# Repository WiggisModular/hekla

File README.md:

# hekla

FeatherWing Eurorack module, optimised for the Feather M4 express. I designed it to act as a slow LFO using DAC0 and DAC1 for two channels. 

## Resources (AKA giants on which shoulder I built)

### Featherwing

https://forum.kicad.info/t/designing-featherwings-in-kicad/6115/2

### Outputs and stuff: 

https://blog.thea.codes/designing-big-honking-button/

BTW: Follow her on twitter, read her blog, buy her modules. Wholesome content from a kickass person.

### Frontpanel copper layer 

Original data https://commons.wikimedia.org/wiki/File:Hekla1980.jpg#/media/File:Hekla1980.jpg

## Production files

Gerber, a schematic and a placement drawing, as well as a BOM and a pick and place file to get the SMD parts assembled over at JLCPCB will be available as releases as soon as I tested the first batch.

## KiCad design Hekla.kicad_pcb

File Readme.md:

# Parsel 

FeatherWing Eurorack module, optimised for the Feather M4 express. I designed it to act as a slow LFO using DAC0 and DAC1 for two channels. 

## Resources (AKA giants on which shoulder I built)

### Featherwing

https://forum.kicad.info/t/designing-featherwings-in-kicad/6115/2

### Outputs and stuff: 

https://blog.thea.codes/designing-big-honking-button/

BTW: Follow her on twitter, read her blog, buy her modules. Wholesome content from a kickass person.

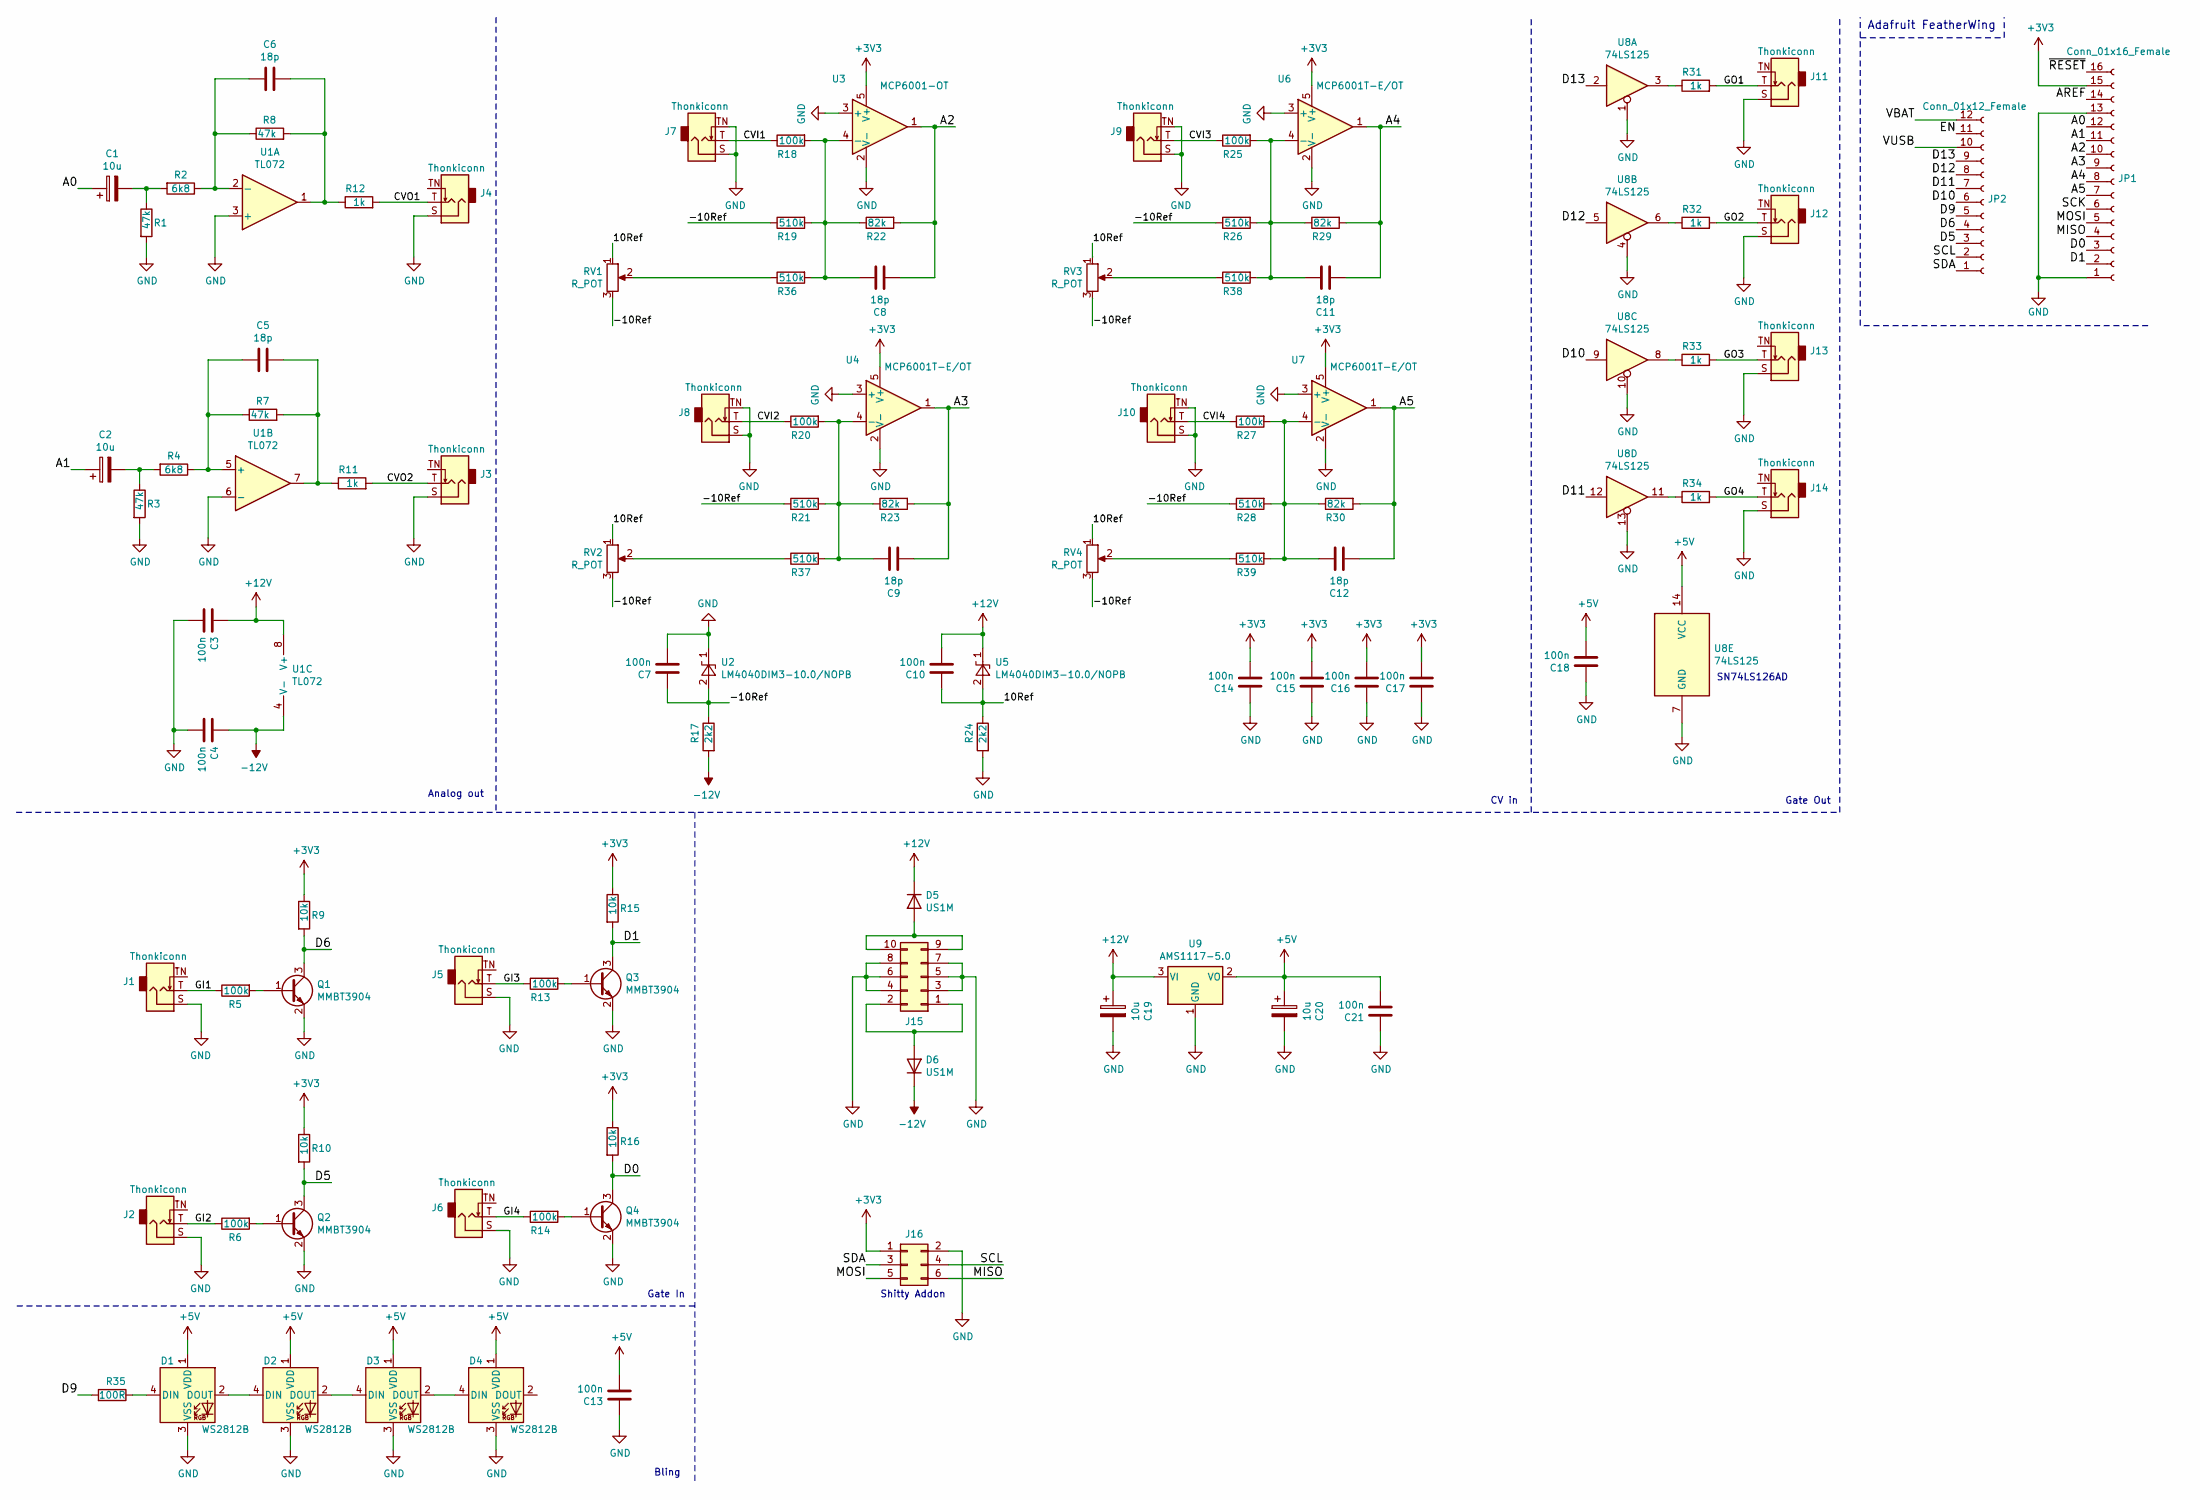
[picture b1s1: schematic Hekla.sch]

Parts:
C1, C2, C19, C20: 10u; CP_Elec_3x5.3; LCSC C249452
C3, C4, C7, C10, C13, C14, C15, C16, C17, C18, C21: 100n; C_0603_1608Metric_Pad1.05x0.95mm_HandSolder; LCSC C14663
C5, C6, C8, C9, C11, C12: 18p; C_0603_1608Metric_Pad1.05x0.95mm_HandSolder; LCSC C1647
D1, D2, D3, D4: WS2812B; LED_WS2812B_PLCC4_5.0x5.0mm_P3.2mm
D5, D6: US1M; D_SMA; LCSC C412437
J1, J2, J3, J4, J5, J6, J7, J8, J9, J10, J11, J12, J13, J14: Thonkiconn; Jack_3.5mm_QingPu_WQP-PJ398SM_Vertical_CircularHoles
J15: Conn_02x05_Odd_Even; PinSocket_2x05_P2.54mm_Vertical
J16: Conn_02x03_Odd_Even; PinSocket_2x03_P2.54mm_Vertical
JP1: Conn_01x16_Female; PinSocket_1x16_P2.54mm_Vertical
JP2: Conn_01x12_Female; PinSocket_1x12_P2.54mm_Vertical
Q1, Q2, Q3, Q4: MMBT3904; SOT-23; LCSC C20526
R1, R3, R7, R8: 47k; R_0603_1608Metric_Pad1.05x0.95mm_HandSolder; LCSC C25819
R2, R4: 6k8; R_0603_1608Metric_Pad1.05x0.95mm_HandSolder; LCSC C23212
R5, R6, R13, R14, R18, R20, R25, R27: 100k; R_0603_1608Metric_Pad1.05x0.95mm_HandSolder; LCSC C25803
R9, R10, R15, R16: 10k; R_0603_1608Metric_Pad1.05x0.95mm_HandSolder; LCSC C25804
R11, R12, R31, R32, R33, R34: 1k; R_0603_1608Metric_Pad1.05x0.95mm_HandSolder; LCSC C21190
R17, R24: 2k2; R_0603_1608Metric_Pad1.05x0.95mm_HandSolder; LCSC C4190
R19, R21, R26, R28, R36, R37, R38, R39: 510k; R_0603_1608Metric_Pad1.05x0.95mm_HandSolder; LCSC C23192
R22, R23, R29, R30: 82k; R_0603_1608Metric_Pad1.05x0.95mm_HandSolder; LCSC C23254
R35: 100R; R_0603_1608Metric_Pad1.05x0.95mm_HandSolder; LCSC C22775
RV1, RV2, RV3, RV4: R_POT; Potentiometer_Alps_RK09L_Single_Vertical
U1: TL072; SOIC-8_3.9x4.9mm_P1.27mm; LCSC C6961
U2, U5: LM4040DIM3-10.0/NOPB; SOT-23; LCSC C129969
U3: MCP6001-OT; SOT-23-5; LCSC C29429
U4, U6, U7: MCP6001T-E/OT; SOT-23-5; LCSC C29429
U8: 74LS125; SOIC-14_3.9x8.7mm_P1.27mm; LCSC C7734
U9: AMS1117-5.0; SOT-223-3_TabPin2; LCSC C6187

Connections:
+3V3: C14.1, C15.1, C16.1, C17.1, J16.1, JP1.15, R9.1, R10.1, R15.1, R16.1, U3.5 (V+), U4.5 (V+), U6.5 (V+), U7.5 (V+)
+5V: C13.1, C18.1, C20.1, C21.1, D1.1 (VDD), D2.1 (VDD), D3.1 (VDD), D4.1 (VDD), U8.14 (VCC), U9.2 (VO)
+12V: C3.2, C10.1, C19.1, D5.1 (K), U1.8 (V+), U5.1 (K), U9.3 (VI)
-12V: C4.2, D6.1 (K), R17.2, U1.4 (V-)
/10Ref: C10.2, R24.1, RV1.1, RV2.1, RV3.1, RV4.1, U5.2 (A)
/-10Ref: C7.2, R17.1, R19.1, R21.1, R26.1, R28.1, RV1.3, RV2.3, RV3.3, RV4.3, U2.2 (A)
/A0: C1.1, JP1.12
/A1: C2.1, JP1.11
/A2: C8.1, JP1.10, R22.2, U3.1
/A3: C9.1, JP1.9, R23.2, U4.1
/A4: C11.1, JP1.8, R29.2, U6.1
/A5: C12.1, JP1.7, R30.2, U7.1
/AREF: JP1.14
/CVI1: J7.T, R18.1
/CVI2: J8.T, R20.1
/CVI3: J9.T, R25.1
/CVI4: J10.T, R27.1
/CVO1: J4.T, R12.2
/CVO2: J3.T, R11.2
/D0: JP1.3, Q4.3 (C), R16.2
/D1: JP1.2, Q3.3 (C), R15.2
/D5: JP2.3, Q2.3 (C), R10.2
/D6: JP2.4, Q1.3 (C), R9.2
/D9: JP2.5, R35.2
/D10: JP2.6, U8.9
/D11: JP2.7, U8.12
/D12: JP2.8, U8.5
/D13: JP2.9, U8.2
/EN: JP2.11
/GI1: J1.T, R5.1
/GI2: J2.T, R6.1
/GI3: J5.T, R13.1
/GI4: J6.T, R14.1
/GO1: J11.T, R31.2
/GO2: J12.T, R32.2
/GO3: J13.T, R33.2
/GO4: J14.T, R34.2
/MISO: J16.6, JP1.4
/MOSI: J16.5, JP1.5
/SCK: JP1.6
/SCL: J16.4, JP2.2
/SDA: J16.3, JP2.1
/VBAT: JP2.12
/VUSB: JP2.10
/~RESET: JP1.16
GND: C3.1, C4.1, C7.1, C13.2, C14.2, C15.2, C16.2, C17.2, C18.2, C19.2, C20.2, C21.2, D1.3 (VSS), D2.3 (VSS), D3.3 (VSS), D4.3 (VSS), J1.S, J2.S, J3.S, J4.S, J5.S, J6.S, J7.S, J7.TN, J8.S, J8.TN, J9.S, J9.TN, J10.S, J10.TN, J11.S, J12.S, J13.S, J14.S, J15.3, J15.4, J15.5, J15.6, J15.7, J15.8, J16.2, JP1.1, JP1.13, Q1.2 (E), Q2.2 (E), Q3.2 (E), Q4.2 (E), R1.2, R3.2, R24.2, U1.3 (+), U1.6 (-), U2.1 (K), U3.2 (V-), U3.3 (+), U4.2 (V-), U4.3 (+), U6.2 (V-), U6.3 (+), U7.2 (V-), U7.3 (+), U8.1, U8.4, U8.7 (GND), U8.10, U8.13, U9.1 (GND)
unnamed: C1.2, R1.1, R2.2
unnamed: C2.2, R3.1, R4.2
unnamed: C5.1, R7.2, R11.1, U1.7
unnamed: C5.2, R4.1, R7.1, U1.5 (+)
unnamed: C6.1, R8.2, R12.1, U1.1
unnamed: C6.2, R2.1, R8.1, U1.2 (-)
unnamed: C8.2, R18.2, R19.2, R22.1, R36.2, U3.4 (-)
unnamed: C9.2, R20.2, R21.2, R23.1, R37.2, U4.4 (-)
unnamed: C11.2, R25.2, R26.2, R29.1, R38.2, U6.4 (-)
unnamed: C12.2, R27.2, R28.2, R30.1, R39.2, U7.4 (-)
unnamed: D1.2 (DOUT), D2.4 (DIN)
unnamed: D1.4 (DIN), R35.1
unnamed: D2.2 (DOUT), D3.4 (DIN)
unnamed: D3.2 (DOUT), D4.4 (DIN)
unnamed: D5.2 (A), J15.9, J15.10
unnamed: D6.2 (A), J15.1, J15.2
unnamed: Q1.1 (B), R5.2
unnamed: Q2.1 (B), R6.2
unnamed: Q3.1 (B), R13.2
unnamed: Q4.1 (B), R14.2
unnamed: R31.1, U8.3
unnamed: R32.1, U8.6
unnamed: R33.1, U8.8
unnamed: R34.1, U8.11
unnamed: R36.1, RV1.2
unnamed: R37.1, RV2.2
unnamed: R38.1, RV3.2
unnamed: R39.1, RV4.2

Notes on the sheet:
Adafruit FeatherWing
Analog out
CV in
Gate Out
Gate In
SN74LS126AD
Bling
Shitty Addon

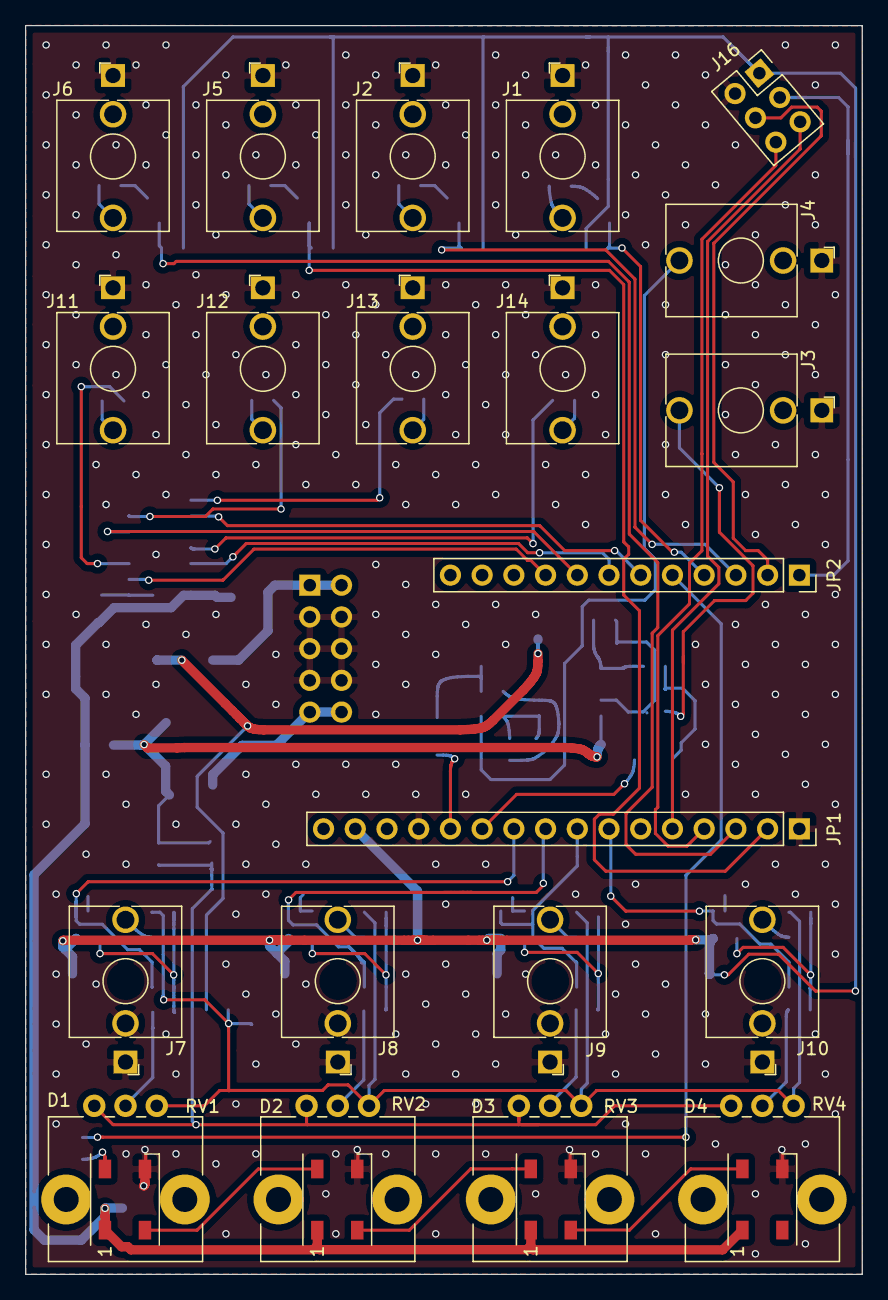
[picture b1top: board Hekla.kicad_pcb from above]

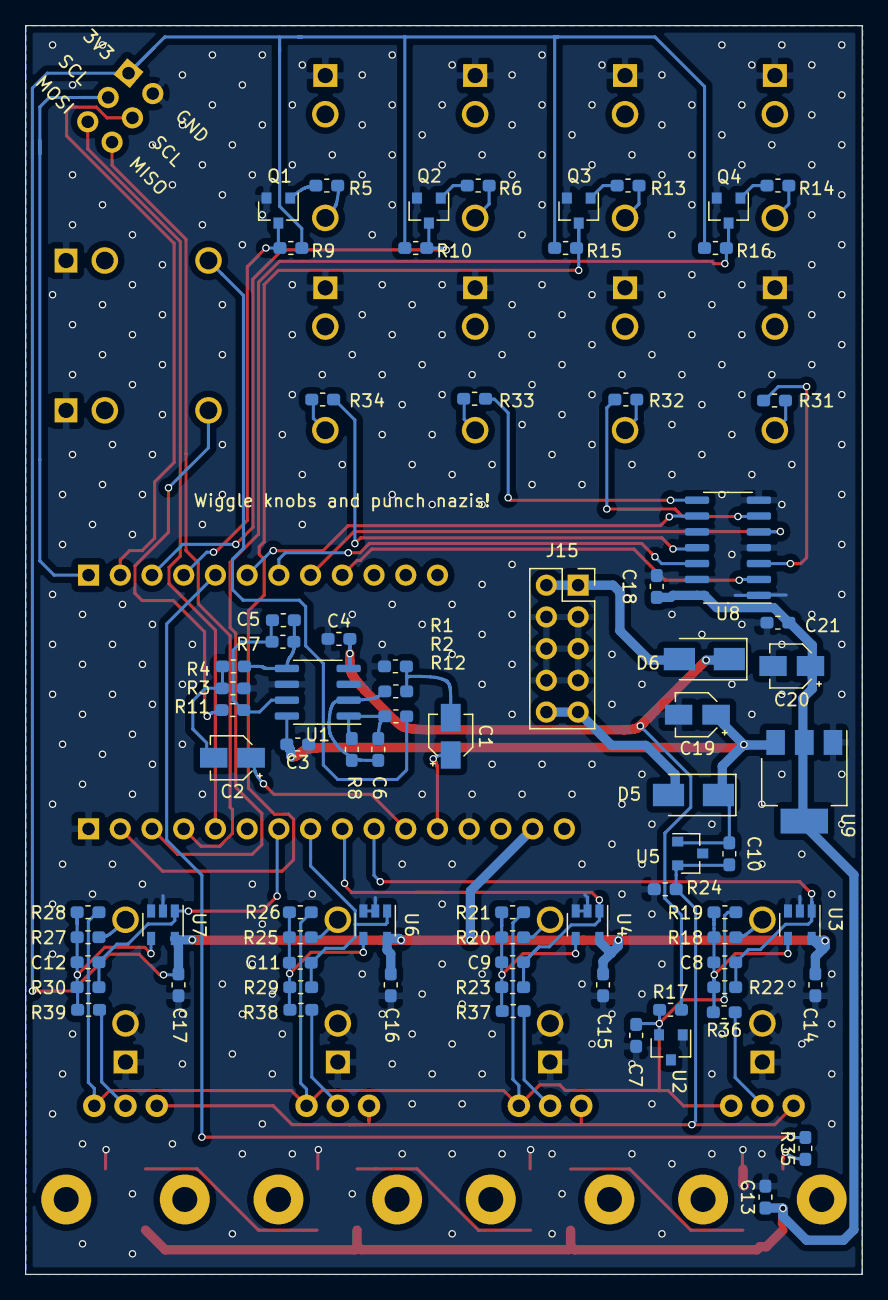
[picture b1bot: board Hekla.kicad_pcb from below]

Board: 2 copper layers, 67.0 x 100.0 mm, 101 parts (76 on the bottom side), 68 nets.

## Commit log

2020-10-13 Readme updated
2020-10-13 gitignore updated
2020-10-13 Panel artwork done
2020-10-13 First revision sent to production
